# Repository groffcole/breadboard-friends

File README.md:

breadboard-friends
==================

A collection of cute breakout boards riding solderless breadboards, mostly for analog audio works

These PCB layouts and schematics are released under a Creative Commons cc-by-sa
3.0 license.

NOTE: This is a forked version of breadboard-friends and has two main differences from the original:
- There are two additional BBFs, one using Thonkiconn 3.5mm Jacks (bbf-thonkjacks) and another providing eurorack header with polarity protection for providing eurorack power to your breadboard from euro bus (bbf-europower). 
- This version has been updated to fit the power rails of the breadboards produced by [Assembly Specialist](http://www.assemblyspecialist.com/). The Assembly Specialist breadboard power rails have a wider spacing between them so the original BBFs do_not fit. Instead of 2x 10 pin DIL male headers for the power rails, use 4x 5 pin SIL male headers.

BBF-EUROPOWER Bill Of Materials (BOM)

- 2x 200ma PTC Poly Fuse or equivalent (or jumper wires if no fuse is required);
- 2x 10uF 25V Electrolytic Caps;
- 2x 1N5818 diodes or equivalent;
- 2x Ferrite Beads;
- 2x 10 Pin DIL male headers;
- 4x 5 pin SIL male headers.

BBF-THONKJACKS Bill Of Materials (BOM)

- 4x Thonkiconn Jacks;
- 1x 8 pin SIL female header;
- 4x 5 pin SIL male headers.

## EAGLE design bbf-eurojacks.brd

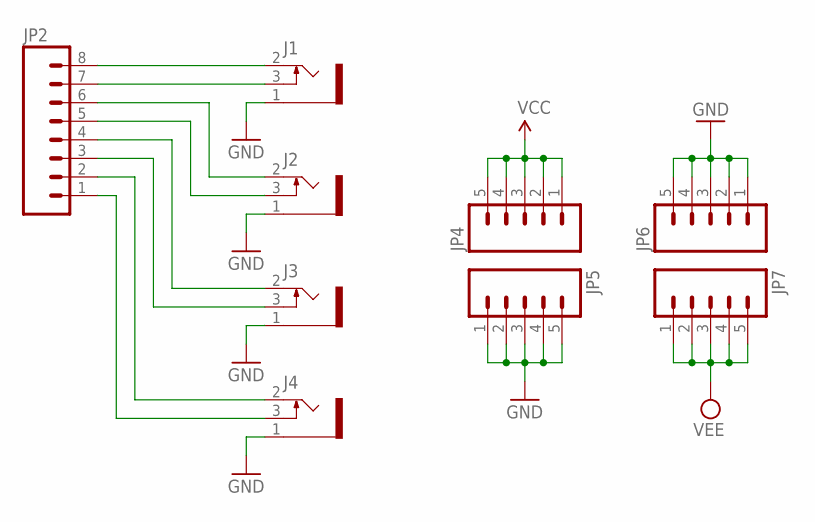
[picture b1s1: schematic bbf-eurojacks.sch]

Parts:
J1, J2, J3, J4: 1502_03SLOTTED; 1502_03_SLOTTED
JP2: M08; 1X08
JP4, JP5, JP6, JP7: M05PTH; 1X05

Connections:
GND: J1.1, J2.1, J3.1, J4.1, JP5.1, JP5.2, JP5.3, JP5.4, JP5.5, JP6.1, JP6.2, JP6.3, JP6.4, JP6.5
unnamed: J2.2, JP2.6
unnamed: J2.3, JP2.5
unnamed: J3.2, JP2.4
unnamed: J3.3, JP2.3
unnamed: J4.2, JP2.2
unnamed: J4.3, JP2.1
unnamed: J1.2, JP2.8
unnamed: J1.3, JP2.7
VCC: JP4.1, JP4.2, JP4.3, JP4.4, JP4.5
VEE: JP7.1, JP7.2, JP7.3, JP7.4, JP7.5

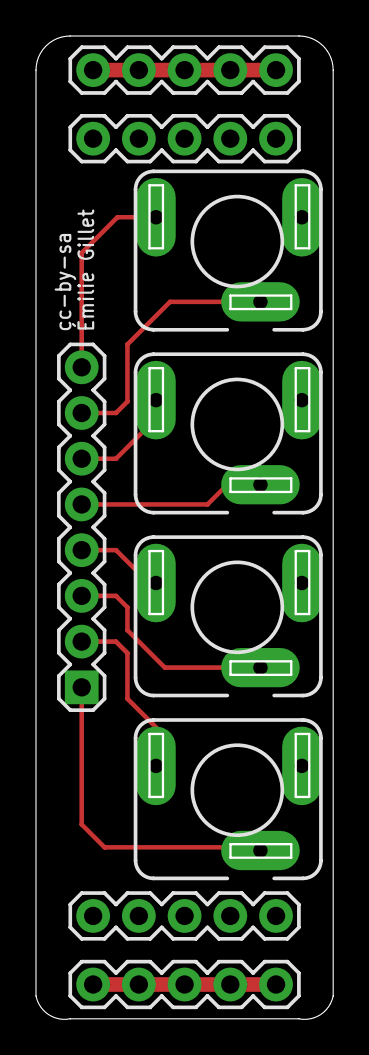
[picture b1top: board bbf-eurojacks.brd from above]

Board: 2 copper layers, 16.4 x 54.5 mm, 9 parts (0 on the bottom side), 11 nets.

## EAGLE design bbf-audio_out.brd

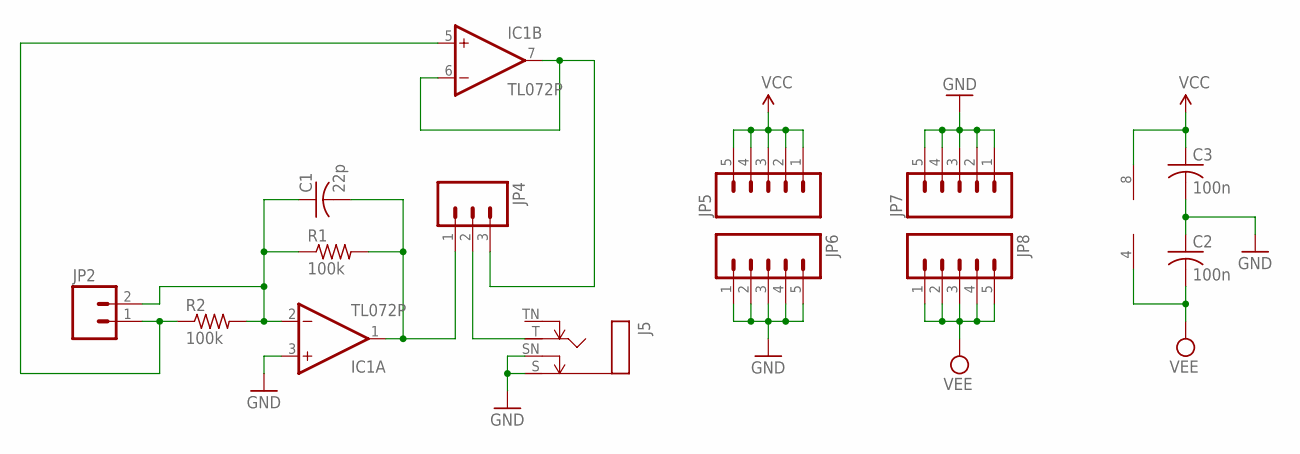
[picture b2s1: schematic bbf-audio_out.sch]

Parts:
C1: 22p; C025-025X050
C2, C3: 100n; C025-025X050
IC1: TL072P; DIL08
J5: MONOSWSLIM; NRJ4HF
JP2: M02PTH; 1X02
JP4: M03PTH; 1X03
JP5, JP6, JP7, JP8: M05PTH; 1X05
R1, R2: 100k; 0204/7

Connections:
GND: C2.1, C3.2, IC1.3 (+IN), J5.S, J5.SN, JP6.1, JP6.2, JP6.3, JP6.4, JP6.5, JP7.1, JP7.2, JP7.3, JP7.4, JP7.5
unnamed: C1.1, IC1.2 (-IN), JP2.2, R1.1, R2.2
unnamed: C1.2, IC1.1 (OUT), JP4.1, R1.2
unnamed: J5.T, JP4.2
unnamed: IC1.5 (+IN), JP2.1, R2.1
unnamed: IC1.6 (-IN), IC1.7 (OUT), JP4.3
VCC: C3.1, IC1.8 (V+), JP5.1, JP5.2, JP5.3, JP5.4, JP5.5
VEE: C2.2, IC1.4 (V-), JP8.1, JP8.2, JP8.3, JP8.4, JP8.5

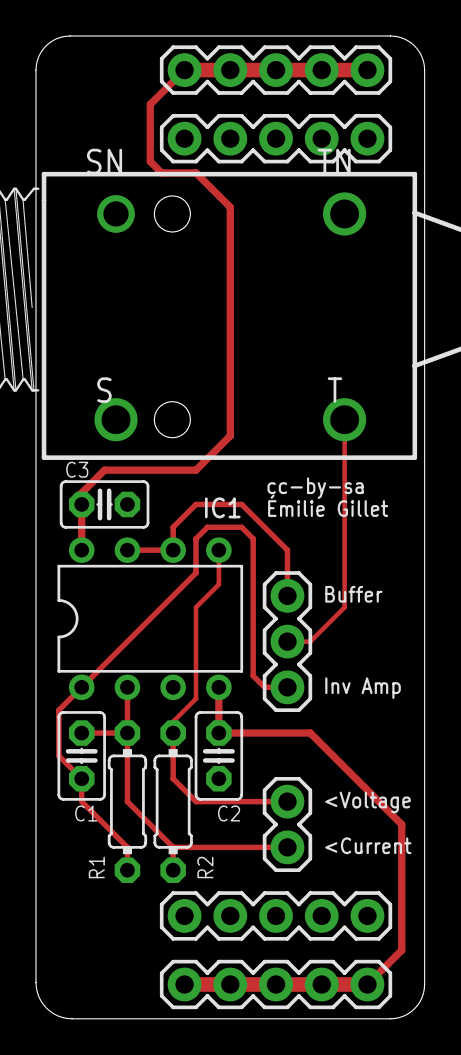
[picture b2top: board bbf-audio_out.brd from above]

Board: 2 copper layers, 21.6 x 54.6 mm, 13 parts (0 on the bottom side), 8 nets.

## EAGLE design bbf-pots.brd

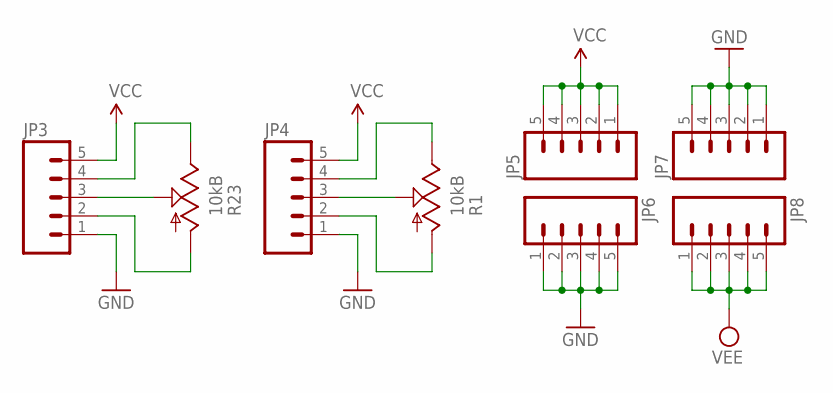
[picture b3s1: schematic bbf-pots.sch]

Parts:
JP3, JP4, JP5, JP6, JP7, JP8: M05PTH; 1X05
R1, R23: 10kB; ALPS_POT_VERTICAL

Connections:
GND: JP3.1, JP4.1, JP6.1, JP6.2, JP6.3, JP6.4, JP6.5, JP7.1, JP7.2, JP7.3, JP7.4, JP7.5
unnamed: JP3.4, R23.P$1 (E)
unnamed: JP3.3, R23.P$2 (S)
unnamed: JP3.2, R23.P$3 (A)
unnamed: JP4.4, R1.P$1 (E)
unnamed: JP4.3, R1.P$2 (S)
unnamed: JP4.2, R1.P$3 (A)
VCC: JP3.5, JP4.5, JP5.1, JP5.2, JP5.3, JP5.4, JP5.5
VEE: JP8.1, JP8.2, JP8.3, JP8.4, JP8.5

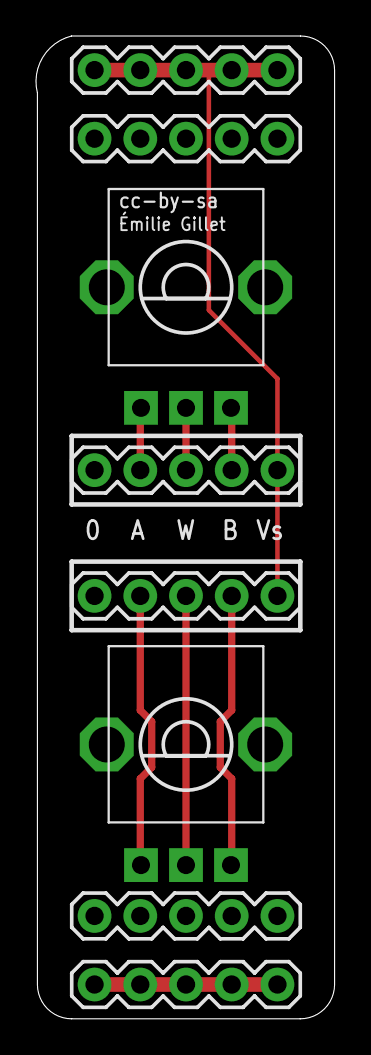
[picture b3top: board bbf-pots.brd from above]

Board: 2 copper layers, 16.6 x 54.6 mm, 8 parts (0 on the bottom side), 9 nets.

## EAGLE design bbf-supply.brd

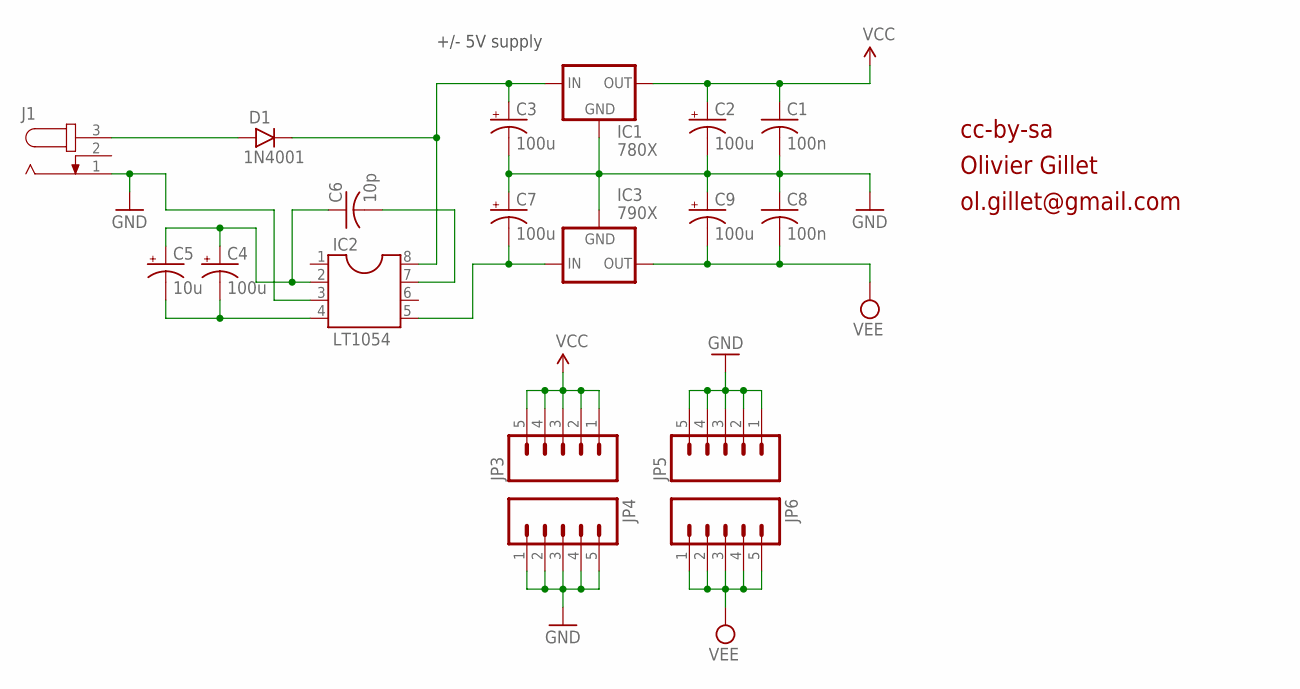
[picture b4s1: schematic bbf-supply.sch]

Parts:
C1, C8: 100n; C025-025X050
C2, C3, C7, C9: 100u; E2,5-7
C4: 100u; E2,5-6
C5: 10u; E2,5-5
C6: 10p; C025-025X050
D1: 1N4001; DO41-3
IC1: 780X; 78XXS
IC2: LT1054; DIL08
IC3: 790X; 79XXS
J1: JACK-PLUG2; SPC4078_BIG_HOLES
JP3, JP4, JP5, JP6: M05PTH; 1X05

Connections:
GND: C1.2, C2.-, C3.-, C7.+, C8.1, C9.+, IC1.GND, IC2.3, IC3.GND, J1.1, JP4.1, JP4.2, JP4.3, JP4.4, JP4.5, JP5.1, JP5.2, JP5.3, JP5.4, JP5.5
unnamed: D1.A, J1.3
unnamed: C3.+, D1.C, IC1.IN, IC2.8
unnamed: C4.+, C5.+, C6.1, IC2.2
unnamed: C4.-, C5.-, IC2.4
unnamed: C6.2, IC2.7
unnamed: C7.-, IC2.5, IC3.IN
VCC: C1.1, C2.+, IC1.OUT, JP3.1, JP3.2, JP3.3, JP3.4, JP3.5
VEE: C8.2, C9.-, IC3.OUT, JP6.1, JP6.2, JP6.3, JP6.4, JP6.5

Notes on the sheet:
cc-by-sa
Olivier Gillet
ol.gillet@gmail.com
+/- 5V supply

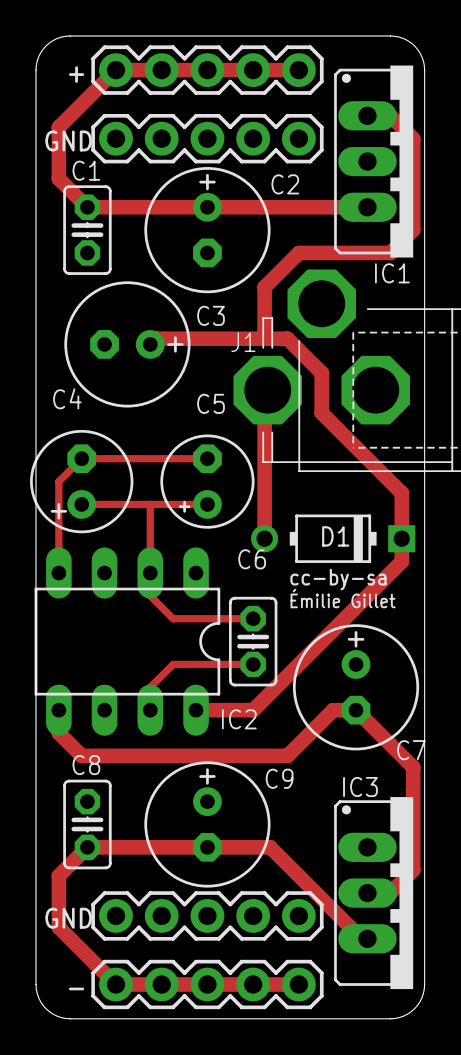
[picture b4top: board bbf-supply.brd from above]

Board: 2 copper layers, 21.6 x 54.6 mm, 18 parts (0 on the bottom side), 9 nets.

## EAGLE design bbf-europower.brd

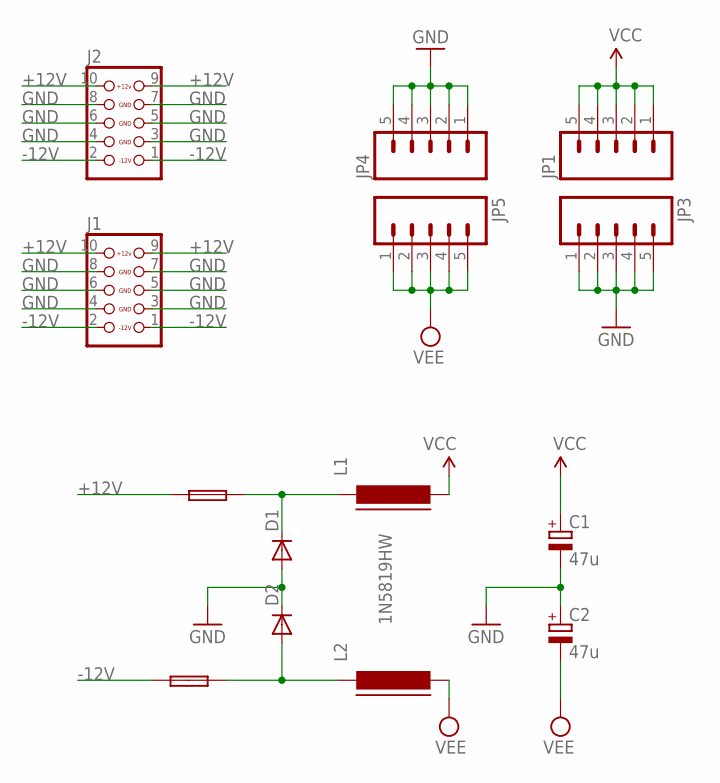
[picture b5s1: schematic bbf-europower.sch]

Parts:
+FUSE1: +FUSE; C050H075X075
-FUSE1: -FUSE; C050H075X075
C1, C2: 47u; E2-5
D1, D2: 1N5819HW; DO35-7
J1, J2: CON_HEADER_2X05-PTH; M2X5
JP1, JP3, JP4, JP5: M05PTH; 1X05
L1, L2: FERRITE-SHORT; FBS

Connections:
+12V: +FUSE1.1, J1.9, J1.10, J2.9, J2.10
-12V: -FUSE1.1, J1.1, J1.2, J2.1, J2.2
GND: C1.-, C2.+, D1.A, D2.C, J1.3, J1.4, J1.5, J1.6, J1.7, J1.8, J2.3, J2.4, J2.5, J2.6, J2.7, J2.8, JP3.1, JP3.2, JP3.3, JP3.4, JP3.5, JP4.1, JP4.2, JP4.3, JP4.4, JP4.5
unnamed: +FUSE1.2, D1.C, L1.1
unnamed: -FUSE1.2, D2.A, L2.1
VCC: C1.+, JP1.1, JP1.2, JP1.3, JP1.4, JP1.5, L1.2
VEE: C2.-, JP5.1, JP5.2, JP5.3, JP5.4, JP5.5, L2.2

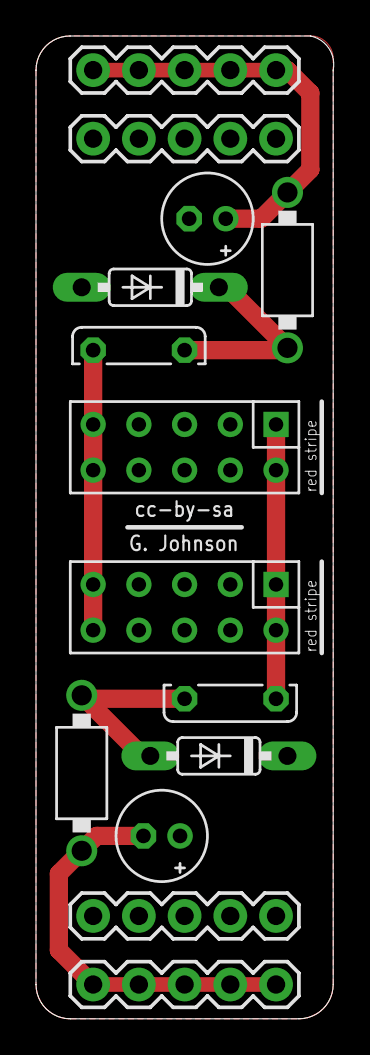
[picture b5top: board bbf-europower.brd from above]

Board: 2 copper layers, 16.5 x 54.6 mm, 14 parts (0 on the bottom side), 7 nets.

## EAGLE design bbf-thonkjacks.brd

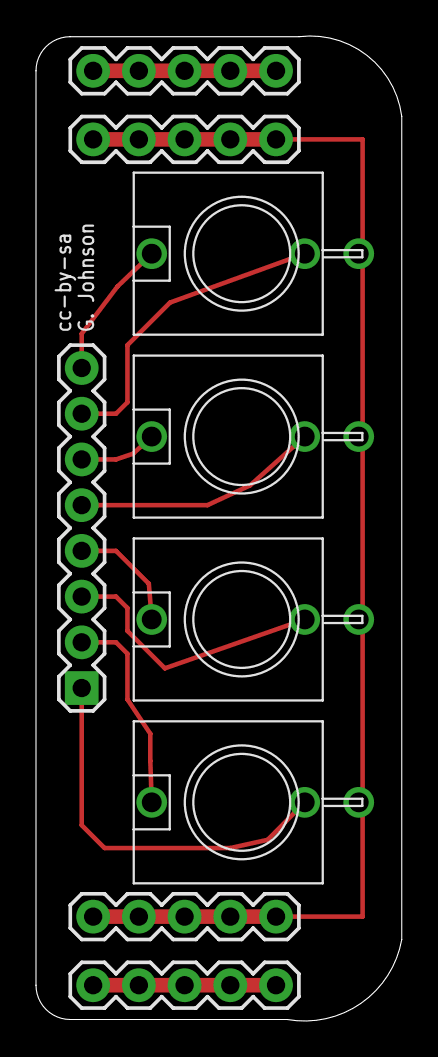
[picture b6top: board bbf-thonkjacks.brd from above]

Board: 2 copper layers, 20.3 x 54.7 mm, 9 parts (0 on the bottom side), 11 nets.

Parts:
J1, J2, J3, J4: WQP-PJ301M-12_JACK
JP2: 1X08
JP4, JP5, JP6, JP7: 1X05

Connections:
GND: J1.P$3, J2.P$3, J3.P$3, J4.P$3, JP4.1, JP4.2, JP4.3, JP4.4, JP4.5, JP6.1, JP6.2, JP6.3, JP6.4, JP6.5
unnamed: J2.P$1, JP2.6
unnamed: J2.P$2, JP2.5
unnamed: J3.P$1, JP2.4
unnamed: J3.P$2, JP2.3
unnamed: J4.P$1, JP2.2
unnamed: J4.P$2, JP2.1
unnamed: J1.P$1, JP2.8
unnamed: J1.P$2, JP2.7
VCC: JP5.1, JP5.2, JP5.3, JP5.4, JP5.5
VEE: JP7.1, JP7.2, JP7.3, JP7.4, JP7.5

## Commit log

2016-08-20 Add files via upload
    Through-hole versions of Thomas Hopman's revision of the bbf-europower.
2016-08-20 Through-hole versions of Thomas Hopman's revision of the bbf-europower.
2020-09-25 adding the new 1x5 connector to ground - first attempt
2020-09-25 the vcc with the farther away connector holes and wider board
2020-09-25 almost there
2020-09-25 finished first draft of europower
2020-10-05 make the original eurojacks rails wider
2020-10-05 thonkiconn jacks wider
2020-10-05 pots more wider
2020-10-05 audio out more wider
2020-10-05 working on supply more wider
2020-10-11 supply more wider
2020-10-11 thonkjacks + and - symbols for the power rails
2020-10-11 remove the + and - symbols from thonkjacks
2020-10-11 make the power rails trace a little less wider
2021-02-17 update names on boards and schematics

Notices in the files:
parts and their libraries:
SparkFun-Aesthetics: Licensing: CC v3.0 Share-Alike You are welcome to use this library for commercial purposes.
